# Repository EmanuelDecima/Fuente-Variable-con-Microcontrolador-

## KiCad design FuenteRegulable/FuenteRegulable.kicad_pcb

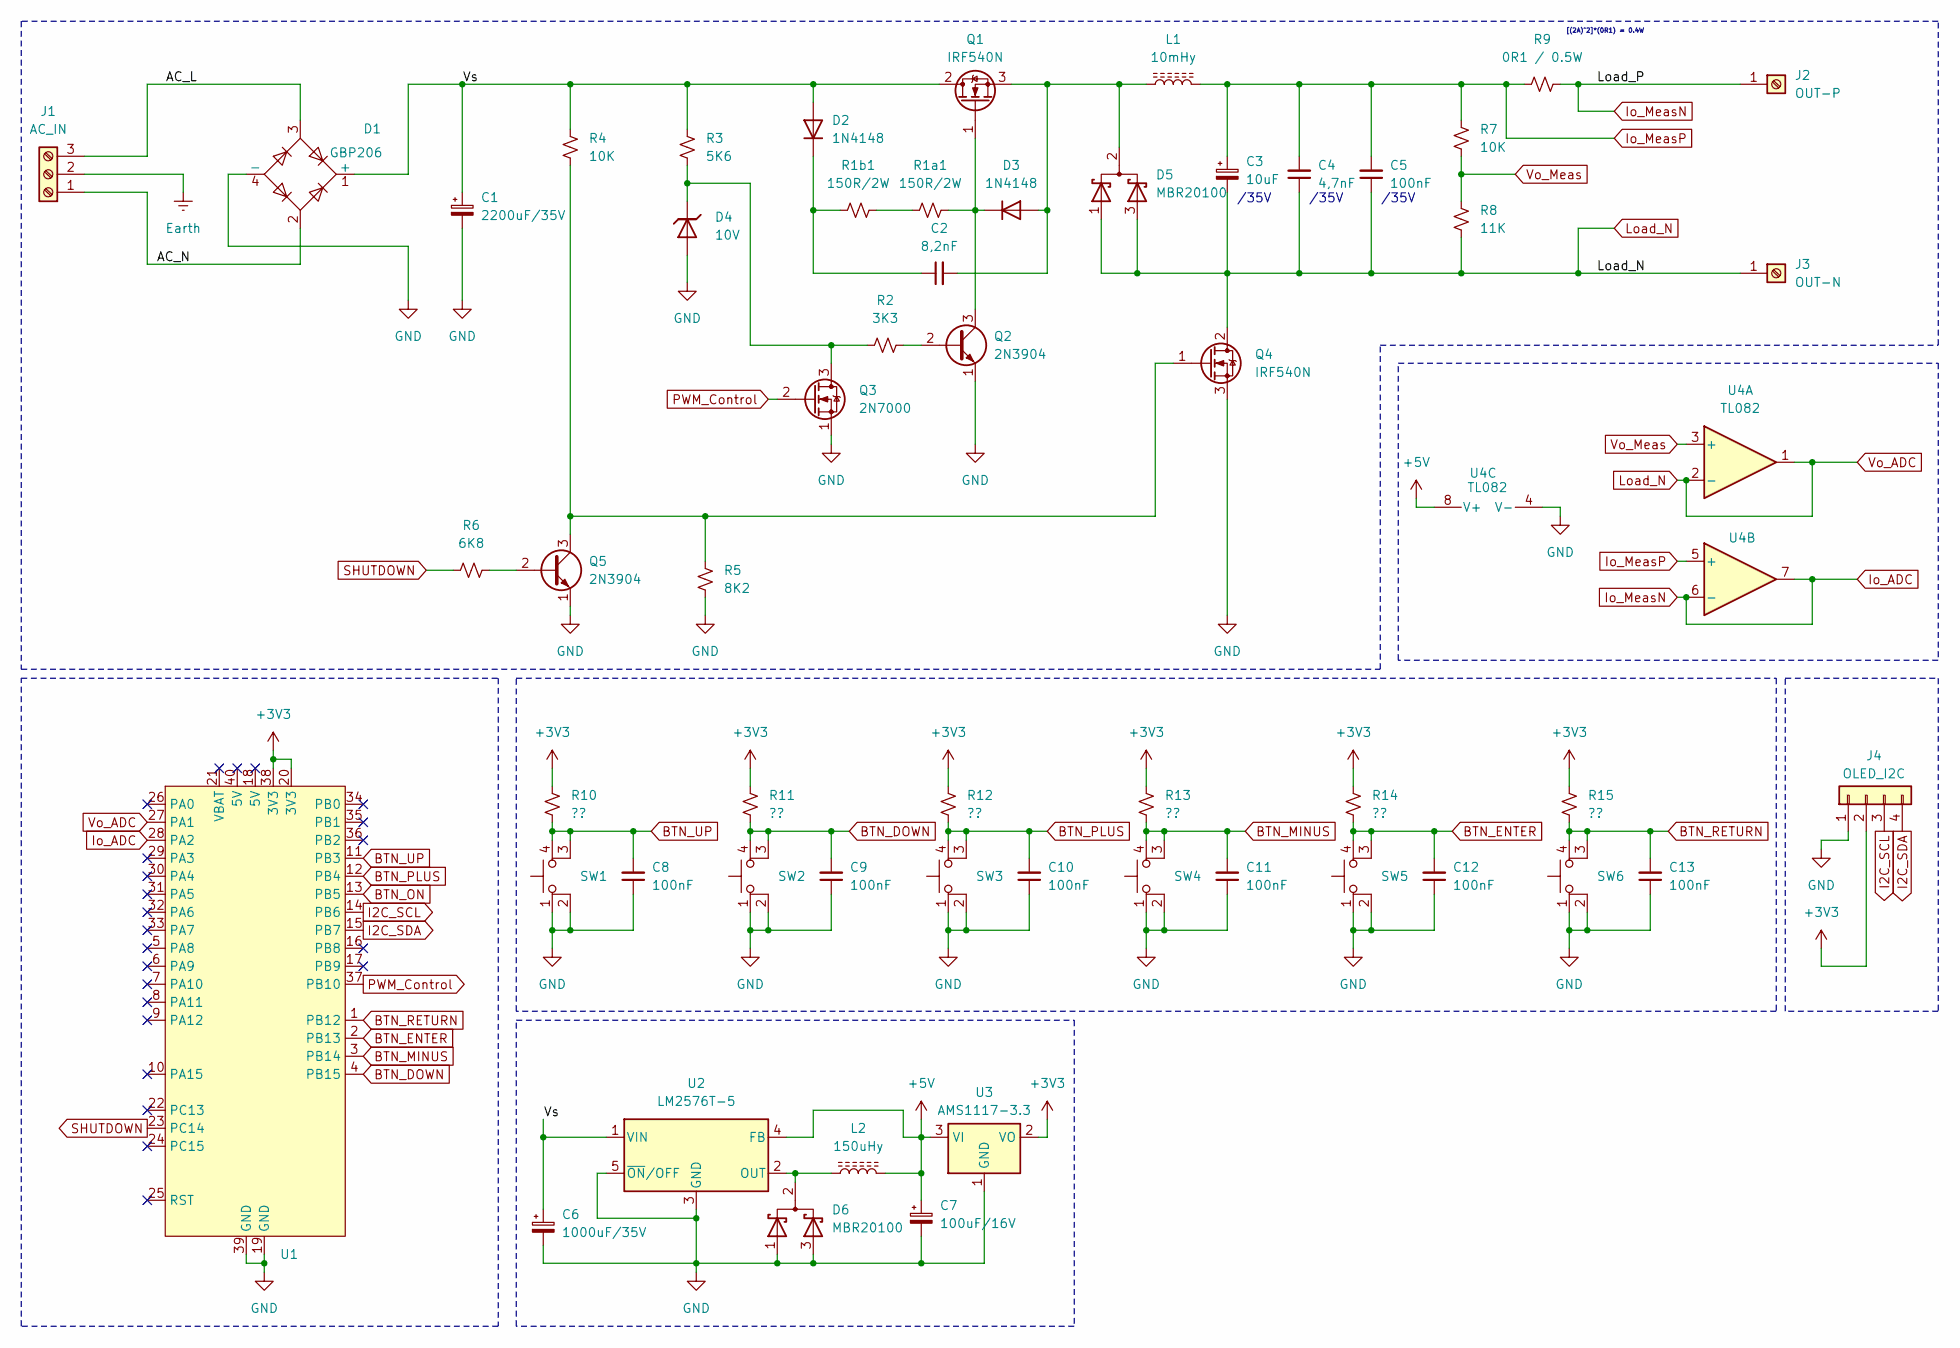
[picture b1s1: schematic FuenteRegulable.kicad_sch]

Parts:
C1: 2200uF/35V; CP_Radial_D16.0mm_P7.50mm
C2: 8,2nF; C_Disc_D3.0mm_W2.0mm_P2.50mm
C3: 10uF; CP_Radial_D4.0mm_P2.00mm
C4: 4,7nF; C_Rect_L7.0mm_W2.0mm_P5.00mm
C5, C8, C9, C10, C11, C12, C13: 100nF; C_Disc_D3.0mm_W2.0mm_P2.50mm
C6: 1000uF/35V; CP_Radial_D14.0mm_P7.50mm
C7: 100uF/16V; CP_Radial_D8.0mm_P5.00mm
D1: GBP206; Diode_Bridge_32.0x5.6x17.0mm_P10.0mm_P7.5mm
D2, D3: 1N4148; D_DO-35_SOD27_P7.62mm_Horizontal
D4: 10V; D_DO-41_SOD81_P10.16mm_Horizontal
D5, D6: MBR20100; TO-220-3_Horizontal_TabDown
J1: AC_IN; TerminalBlock_Phoenix_MKDS-1,5-3-5.08_1x03_P5.08mm_Horizont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
J2: OUT-P; SolderWirePad_1x01_SMD_5x10mm
J3: OUT-N; SolderWirePad_1x01_SMD_5x10mm
J4: OLED_I2C; PinSocket_1x04_P2.54mm_Vertical
L1: 10mHy; L_Toroid_Vertical_L16.0mm_W8.0mm_P7.62mm
L2: 150uHy; L_Toroid_Vertical_L16.0mm_W8.0mm_P7.62mm
Q1, Q4: IRF540N; TO-220-3_Vertical
Q2, Q5: 2N3904; TO-92_Wide
Q3: 2N7000; TO-92_Wide
R1a1, R1b1: 150R/2W; R_Axial_DIN0614_L14.3mm_D5.7mm_P15.24mm_Horizontal
R2: 3K3; R_Axial_DIN0207_L6.3mm_D2.5mm_P7.62mm_Horizontal
R3: 5K6; R_Axial_DIN0207_L6.3mm_D2.5mm_P7.62mm_Horizontal
R4, R7: 10K; R_Axial_DIN0207_L6.3mm_D2.5mm_P7.62mm_Horizontal
R5: 8K2; R_Axial_DIN0207_L6.3mm_D2.5mm_P7.62mm_Horizontal
R6: 6K8; R_Axial_DIN0207_L6.3mm_D2.5mm_P7.62mm_Horizontal
R8: 11K; R_Axial_DIN0207_L6.3mm_D2.5mm_P7.62mm_Horizontal
R9: 0R1 / 0.5W; R_Axial_DIN0411_L9.9mm_D3.6mm_P12.70mm_Horizontal
R10, R11, R12, R13, R14, R15: ??; R_Axial_DIN0207_L6.3mm_D2.5mm_P7.62mm_Horizontal
SW1, SW2, SW3, SW4, SW5, SW6: SW_MEC_5E; SW_MEC_5GSH9
U1: STM32BlackPill
U2: LM2576T-5; TO-220-5_Vertical
U3: AMS1117-3.3; SOT-223-3_TabPin2
U4: TL082; DIP-8_W7.62mm

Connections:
+3V3: J4.2, R10.2, R11.2, R12.2, R13.2, R14.2, R15.2, U1.20 (3V3), U1.38 (3V3), U3.2 (VO)
+5V: C7.1, L2.2, U2.4 (FB), U3.3 (VI), U4.8 (V+)
/AC_L: D1.3, J1.3
/AC_N: D1.2, J1.1
/Vs: C1.1, C6.1, D1.1 (+), D2.2 (A), Q1.2 (D), R3.2, R4.2, U2.1 (VIN)
BTN_DOWN: C9.2, R11.1, SW2.3 (K), SW2.4 (A), U1.4 (PB15)
BTN_ENTER: C12.2, R14.1, SW5.3 (K), SW5.4 (A), U1.2 (PB13)
BTN_MINUS: C11.2, R13.1, SW4.3 (K), SW4.4 (A), U1.3 (PB14)
BTN_ON: U1.13 (PB5)
BTN_PLUS: C10.2, R12.1, SW3.3 (K), SW3.4 (A), U1.12 (PB4)
BTN_RETURN: C13.2, R15.1, SW6.3 (K), SW6.4 (A), U1.1 (PB12)
BTN_UP: C8.2, R10.1, SW1.3 (K), SW1.4 (A), U1.11 (PB3)
Earth: J1.2
GND: C1.2, C6.2, C7.2, C8.1, C9.1, C10.1, C11.1, C12.1, C13.1, D1.4 (-), D4.2 (A), D6.1 (A), D6.3 (A), J4.1, Q2.1 (E), Q3.1 (S), Q4.3 (S), Q5.1 (E), R5.1, SW1.1, SW1.2, SW2.1, SW2.2, SW3.1, SW3.2, SW4.1, SW4.2, SW5.1, SW5.2, SW6.1, SW6.2, U1.19 (GND), U1.39 (GND), U2.3 (GND), U2.5 (~ON/OFF), U3.1 (GND), U4.4 (V-)
I2C_SCL: J4.3, U1.14 (PB6)
I2C_SDA: J4.4, U1.15 (PB7)
Io_ADC: J2.1, R9.1, U1.28 (PA2), U4.6 (-), U4.7
Io_MeasP: C3.1, C4.2, C5.2, L1.2, R7.2, R9.2, U4.5 (+)
Load_N: C3.2, C4.1, C5.1, D5.1 (A), D5.3 (A), J3.1, Q4.2 (D), R8.1, U1.27 (PA1), U4.1, U4.2 (-)
unnamed: C2.1, D2.1 (K), R1b1.1
unnamed: C2.2, D3.2 (A), D5.2 (K), L1.1, Q1.3 (S)
unnamed: D3.1 (K), Q1.1 (G), Q2.3 (C), R1a1.2
unnamed: D4.1 (K), Q3.3 (D), R2.1, R3.1
unnamed: D6.2 (K), L2.1, U2.2 (OUT)
unnamed: Q2.2 (B), R2.2
unnamed: Q4.1 (G), Q5.3 (C), R4.1, R5.2
unnamed: Q5.2 (B), R6.2
unnamed: R1a1.1, R1b1.2
PWM_Control: Q3.2 (G), U1.37 (PB10)
SHUTDOWN: R6.1, U1.23 (PC14)
Vo_Meas: R7.1, R8.2, U4.3 (+)

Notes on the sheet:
/35V
[(2A)^2]*(0R1) = 0.4W

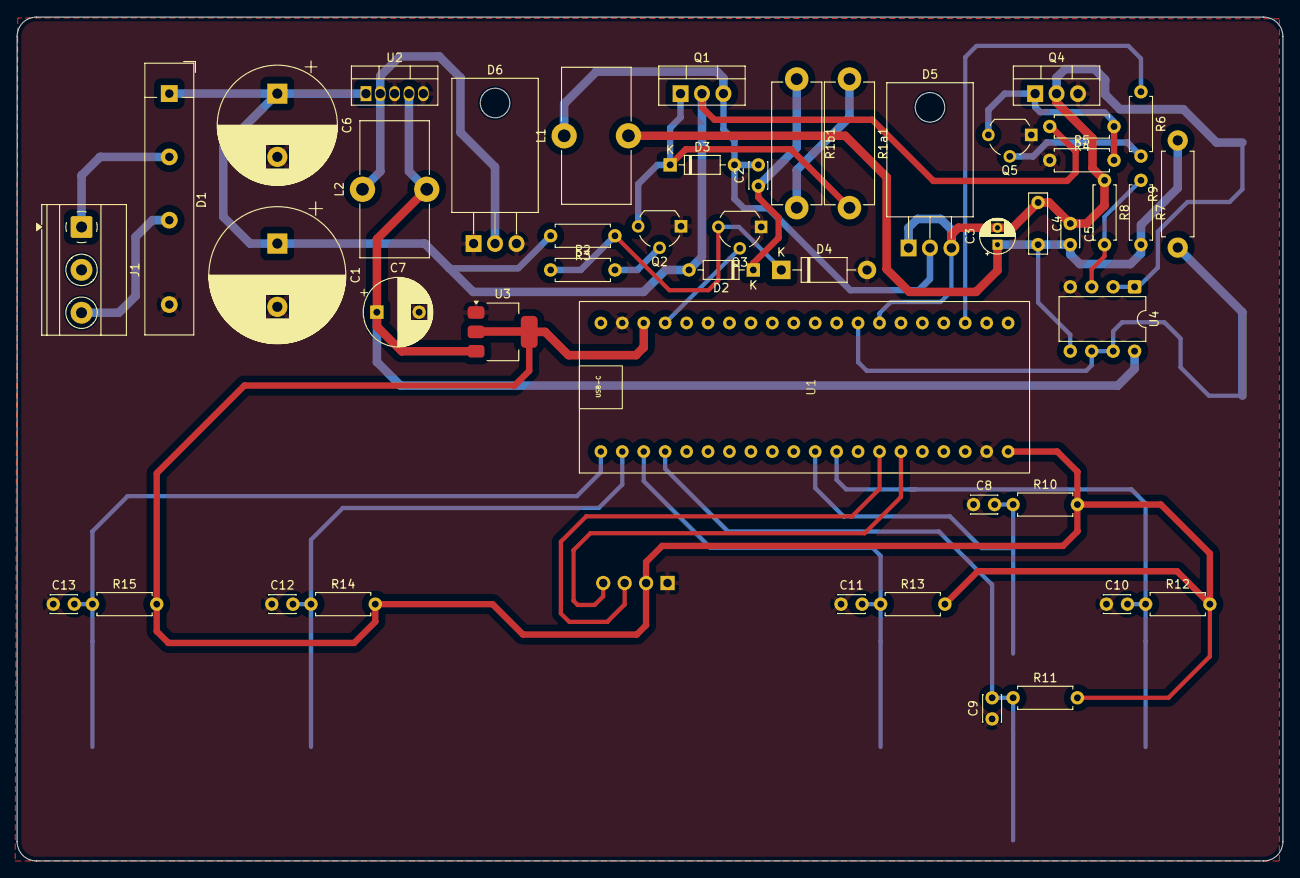
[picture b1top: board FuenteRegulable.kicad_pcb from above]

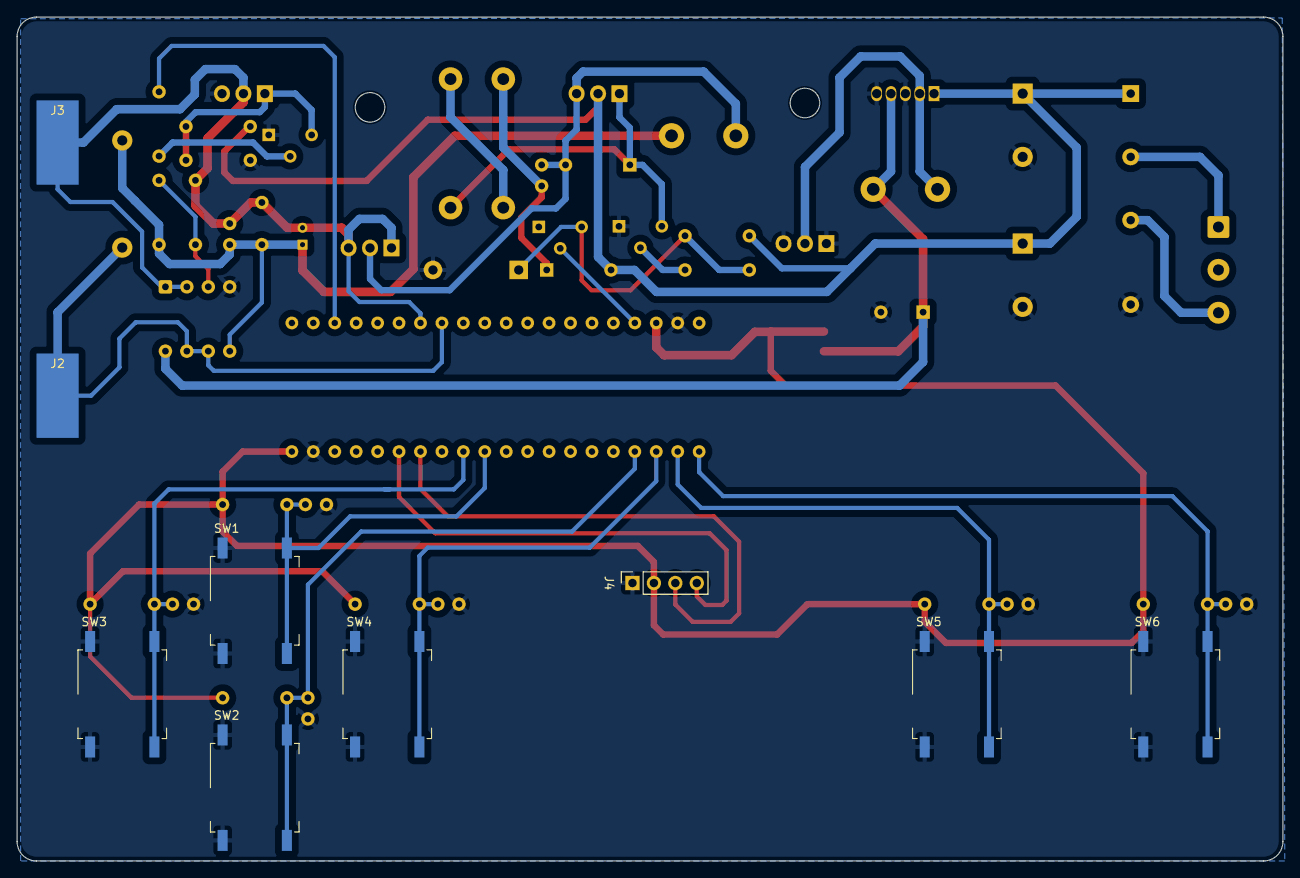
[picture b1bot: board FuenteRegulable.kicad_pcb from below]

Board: 2 copper layers, 150.0 x 100.0 mm, 56 parts (9 on the bottom side), 29 nets.

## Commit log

2025-11-07 Inicio de proyecto
2025-11-07 Simulacion de puente de diodos y filtro capacitivo principal
2025-11-07 Simulacion de fusible electronico
2025-11-12 Rediseño de fusible electronico-baja su consumo
2025-11-13 Diagrama esquematico terminado
2025-11-13 Documentacion-solo plantilla
2025-11-13 Comienzo a rutear PCB
2025-11-13 PCB Terminado
